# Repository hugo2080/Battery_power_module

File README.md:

# Battery_power_module

Battery power module for bathroom scale

Place a 0.7 V forward voltage rectifier diode, e.g. 1N4007, between pin 2 of connector J2 and VDD of the MCU board, with the anode facing J2, to reduce the voltage to a safe 3.6 V.

## Licensing

This project is released under the **CERN Open Hardware Licence v1.2**.

* **Hardware Documentation:** Licensed under the terms of CERN OHL v.1.2. See `cern_ohl_v_1_2.txt` for the full license text.
* **Software/Firmware:** none.
* **Documentation Location:** https://github.com/hugo2080/Battery_power_module

> **Note:** As per the license requirements, any redistribution or modification of this project must retain the original copyright notices and the license text.

## Repository Structure

Based on the project configuration, the files are organized as follows:

* `/hardware` – KiCad source files (`.kicad_sch`, `.kicad_pcb`).
* `/datasheets` – Placeholder for component datasheets (this folder is empty due to manufacturer copyrights; please download them manually for your own use).
* `/software` – Firmware source code and scripts.
* `CHANGES.TXT` – A log of modifications (required by CERN OHL).
* `PRODUCT.TXT` – Contact information for the author and potential manufacturers.

## Technical Requirements

* **PCB Design:** KiCad (version 9.0 or newer recommended).
* **Firmware/Software:** none.

## Getting Started

1.  **Clone the repository:** `git clone https://github.com/hugo2080/Battery_power_module`
2.  **Open the hardware project:** Navigate to the `/hardware` folder and open the `.kicad_pro` file in KiCad.
3.  **Prepare for assembly:** Refer to the Bill of Materials (BOM) and download the necessary datasheets into the `/datasheets` folder.

## Disclaimer

This documentation is distributed **WITHOUT ANY EXPRESS OR IMPLIED WARRANTY**, including of merchantability, satisfactory quality, and fitness for a particular purpose. Use this hardware at your own risk. Please see the CERN OHL v.1.2 for applicable conditions.

---
Copyright hugo2080 2025

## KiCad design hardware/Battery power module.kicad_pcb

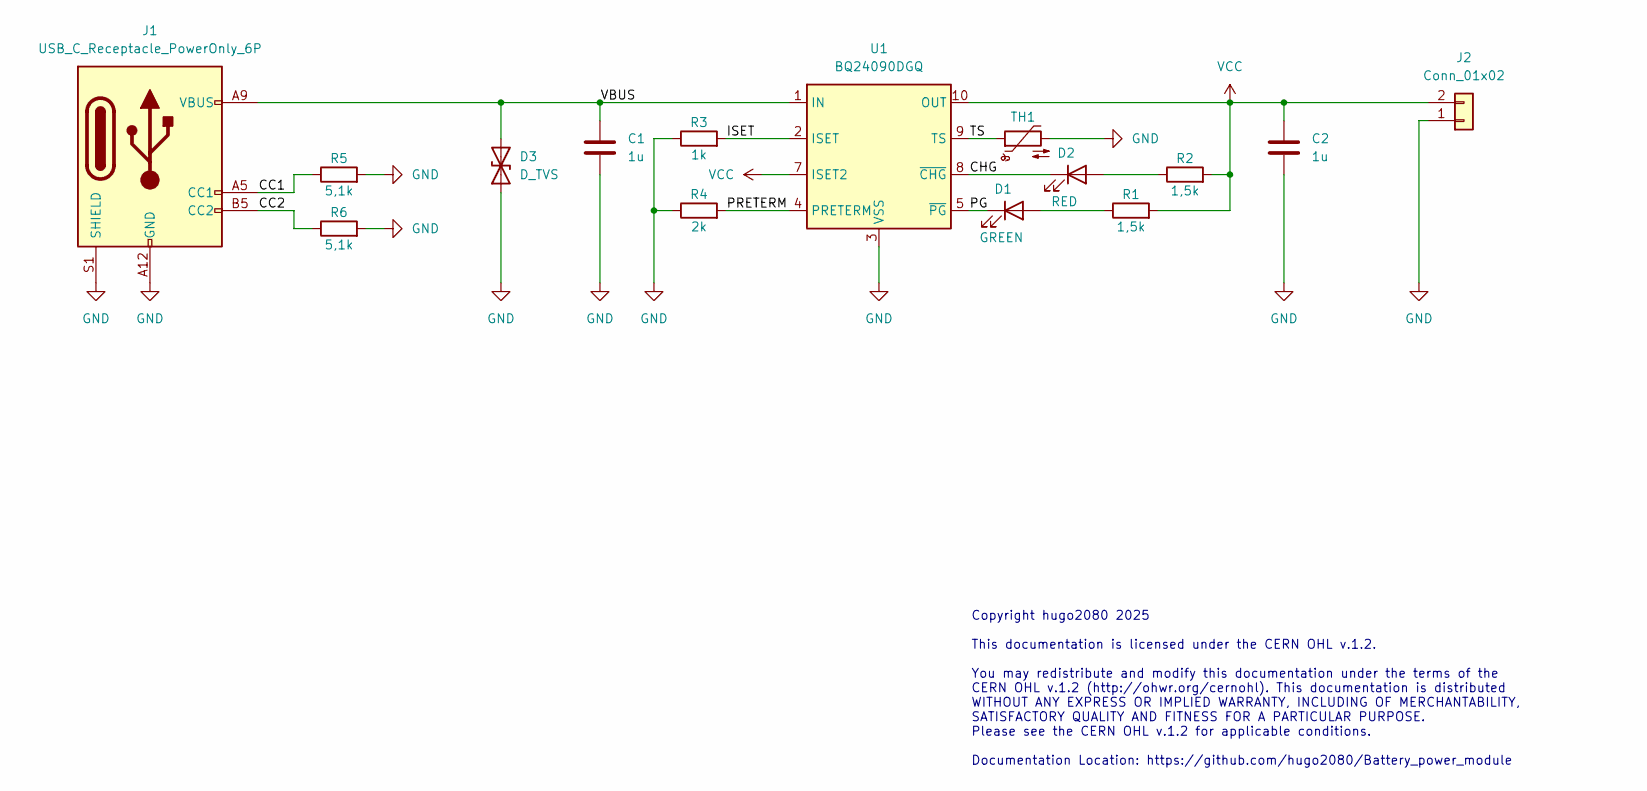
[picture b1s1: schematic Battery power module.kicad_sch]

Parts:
C1, C2: 1u; C_0603_1608Metric
D1: GREEN; LED_0805_2012Metric
D2: RED; LED_0805_2012Metric
D3: D_TVS; D_SMB
J1: USB_C_Receptacle_PowerOnly_6P; USB_C_Receptacle_GCT_USB4125-xx-x-0190_6P_TopMnt_Horizontal
J2: Conn_01x02; JST_PH_B2B-PH-K_1x02_P2.00mm_Vertical
R1, R2: 1,5k; R_0603_1608Metric
R3: 1k; R_0603_1608Metric
R4: 2k; R_0603_1608Metric
R5, R6: 5,1k; R_0603_1608Metric
TH1: Thermistor_NTC; R_Axial_DIN0207_L6.3mm_D2.5mm_P2.54mm_Vertical
U1: BQ24090DGQ; HVSSOP-10-1EP_3x3mm_P0.5mm_EP1.57x1.88mm_ThermalVias

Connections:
/CC1: J1.A5 (CC1), R5.1
/CC2: J1.B5 (CC2), R6.1
/CHG: D2.1 (K), U1.8 (~CHG)
/ISET: R3.2, U1.2 (ISET)
/PG: D1.1 (K), U1.5 (~PG)
/PRETERM: R4.2, U1.4 (PRETERM)
/TS: TH1.1, U1.9 (TS)
/VBUS: C1.1, D3.2 (A2), J1.A9 (VBUS), J1.B9 (VBUS), U1.1 (IN)
GND: C1.2, C2.2, D3.1 (A1), J1.A12 (GND), J1.B12 (GND), J1.S1 (SHIELD), J2.1, R3.1, R4.1, R5.2, R6.2, TH1.2, U1.3 (VSS), U1.11 (VSS)
unnamed: D1.2 (A), R1.1
unnamed: D2.2 (A), R2.1
VCC: C2.1, J2.2, R1.2, R2.2, U1.7 (ISET2), U1.10 (OUT)

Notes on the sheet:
Copyright hugo2080 2025 This documentation is licensed under the CERN OHL v.1.2. You may redistribute and modify this documentation under the terms of the CERN OHL v.1.2 (http://ohwr.org/cernohl). This documentation is distributed WITHOUT ANY EXPRESS OR IMPLIED WARRANTY, INCLUDING OF MERCHANTABILIT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

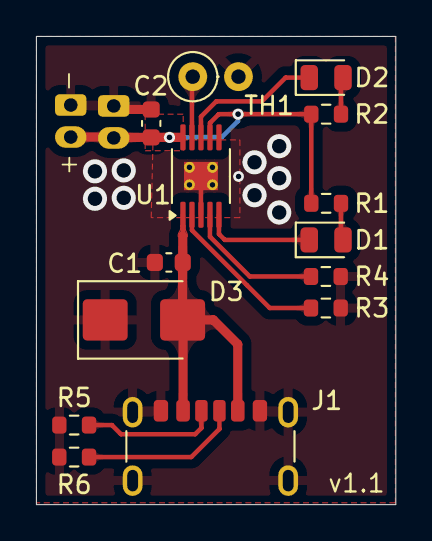
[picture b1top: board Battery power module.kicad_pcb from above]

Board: 2 copper layers, 20.0 x 26.0 mm, 14 parts (0 on the bottom side), 12 nets.

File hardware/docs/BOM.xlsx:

Reference | Qty | Value | DNP | Exclude from BOM | Exclude from Board | Footprint | Datasheet
C1,C2 | 2 | 1u |  |  |  | Capacitor_SMD:C_0603_1608Metric | ~
D1 | 1 | GREEN |  |  |  | LED_SMD:LED_0805_2012Metric | ~
D2 | 1 | RED |  |  |  | LED_SMD:LED_0805_2012Metric | ~
D3 | 1 | D_TVS |  |  |  | Diode_SMD:D_SMB | ~
J1 | 1 | USB_C_Receptacle_PowerOnly_6P |  |  |  | Connector_USB:USB_C_Receptacle_GCT_USB4125-xx-x-0190_6P_TopMnt_Horizontal | https://www.usb.org/sites/default/files/documents/usb_type-c.zip
R1,R2 | 2 | 1,5k |  |  |  | Resistor_SMD:R_0603_1608Metric | ~
R3 | 1 | 1k |  |  |  | Resistor_SMD:R_0603_1608Metric | ~
R4 | 1 | 2k |  |  |  | Resistor_SMD:R_0603_1608Metric | ~
R5,R6 | 2 | 5,1k |  |  |  | Resistor_SMD:R_0603_1608Metric | ~
TH1 | 1 | Thermistor_NTC |  |  |  | Resistor_THT:R_Axial_DIN0207_L6.3mm_D2.5mm_P2.54mm_Vertical | ~
U1 | 1 | BQ24090DGQ |  |  |  | Package_SO:HVSSOP-10-1EP_3x3mm_P0.5mm_EP1.57x1.88mm_ThermalVias | http://www.ti.com/lit/ds/symlink/bq24090.pdf

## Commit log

2025-11-29 Add Battery power module-fancy.rar to .gitignore
2025-11-29 Add TVS & finish ver. 1.0
2025-11-29 Add license
2026-02-01 Version 1.0: Hardware files and CERN OHL v1.2 license
2026-02-01 Correcting typos
2026-02-01 Correcting typos 2
2026-02-01 Correcting typos 3
2026-02-06 Add Battery calculation sheet
2026-02-06 Add ibom.html
2026-02-06 Add nets and tracks to ibom.html
2026-02-23 Add BOM
2026-03-15 Version 1.1: Extending the USB port beyond the board outline and adding a version designation on the PCB

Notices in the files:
hardware/Battery power module.kicad_pcb:
Licensed under CERN OHL v.1.2
